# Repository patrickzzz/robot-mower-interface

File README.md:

# Robot Mower Interface

## Overview
This project provides an interface for controlling and managing a robot mower.

Initially this is done for a Ferrex R800Easy+ robot mower (meaning, it will be probably easily adaptable to other models from Ferrex, Yard Force (Yardforce), Garden Feelings and so on). 

## Original Goals
- The mower lacks the possibility to mow less than 4 hours a day. Also it has no app to control it (other models may have an app, but only closed source). These are the main reasons for this project.
- The main goal is a personal use case. There still might be errors in the project and/or in the documentation.

## Features
- **Control**: Execute Start, Home, Stop, and Lock on the mower.
- **Configuration**: Configure Wi-Fi settings (either connected to a Wifi, or as Access Point).
- **Scheduling**: Set mowing schedules.
- **Status**: View mower status
- **Logs**: See logs from the mower
- **API** Access all features via API
- **Web Interface** Access all features via a web interface
- **OTA Updates** Update the firmware and filesystem of the mower interface over the air (OTA) in Webinterface or API Endpoint.

## Demo of first running version

## License
This project is licensed under the Creative Commons Zero v1.0 Universal (CC0 1.0) - see the [LICENSE](LICENSE) file for details.

It's important to note that the original firmware of the mower is not open source, and this project is not affiliated with the manufacturer.
The original firmware of the mower is not changed in any way, but the warranty of the mower will be voided modifying the mower in this way.
I am not responsible for any damage to the mower or any other device.

## API Endpoint Documentation

### 1. `/start`
- **Method:** `POST`
- **Description:** Starts the mower.
- **Parameters:** None
- **Response:** `200 OK` if successful

### 2. `/home`
- **Method:** `POST`
- **Description:** Sends the mower back to the charging station.
- **Parameters:** None
- **Response:** `200 OK` if successful

### 3. `/stop`
- **Method:** `POST`
- **Description:** Stops the mower.
- **Parameters:** None
- **Response:** `200 OK` if successful

### 4. `/lock`
- **Method:** `POST`
- **Description:** Locks the mower.
- **Parameters:** None
- **Response:** `200 OK` if successful

### 5. `/unlock`
- **Method:** `POST`
- **Description:** Unlocks the mower.
- **Parameters:** None
- **Response:** `200 OK` if successful

### 6. `/status`
- **Method:** `GET`
- **Description:** Returns the current status of the mower.
- **Parameters:** None
- **Response:** JSON object with the following fields:
    - `date`: Current date on the mower
    - `time`: Current time on the mower
    - `isCharging`: Charging status
    - `isLocked`: Lock status
    - `isEmergency`: Emergency status
    - `isIdle`: Idle status
    - `isAccessPoint`: Access Point mode status
    - `hostname`: Hostname of the mower
    - `ssid`: Current WiFi SSID
    - `ip`: IP address of the mower
    - `mowingPlanActive`: Indicates if the mowing plan is active

### 7. `/mowing-plan`
- **Method:** `GET`
- **Description:** Retrieves the current mowing plan.
- **Parameters:** None
- **Response:** JSON file of the mowing plan if exists, or `204 No Content` if not found

### 8. `/mowing-plan`
- **Method:** `POST`
- **Description:** Sets a new mowing plan.
- **Payload:** JSON object with the following fields:
    - `customMowingPlanActive` (boolean): Activates or deactivates the custom mowing plan
    - `days` (array of booleans): Specifies active days (Mon-Sun)
    - `planTimeStart` (string): Mowing start time (e.g., `"09:00"`)
    - `planTimeEnd` (string): Mowing end time (e.g., `"17:00"`)
- **Response:** `200 OK` if successful, `400 Bad Request` if parameters are missing

### 9. `/wifis`
- **Method:** `GET`
- **Description:** Returns a list of available WiFi networks.
- **Parameters:** None
- **Response:** JSON array with SSIDs of the detected networks

### 10. `/wifi`
- **Method:** `POST`
- **Description:** Sets the WiFi credentials for the mower to connect to.
- **Payload:** JSON object with the following fields:
    - `ssid` (string): WiFi SSID
    - `password` (string): WiFi password
- **Response:** `200 OK` if successful, `400 Bad Request` if parameters are missing

### 11. `/date-time`
- **Method:** `POST`
- **Description:** Sets the date and time on the mower.
- **Payload:** JSON object with the following fields:
    - `date` (string): Date in the format `YYYY-MM-DD`
    - `time` (string): Time in the format `HH:MM`
- **Response:** `200 OK` if successful, `400 Bad Request` if parameters are missing

### 12. `/update`
- **Method:** `POST`
- **Description:** Allows for simultaneous upload and update of both firmware and filesystem files on the device. This endpoint manages both types of updates, determining the file type based on the filename.
- **Payload:** Multipart form-data with up to two files:
  - `firmware.bin`: Firmware binary file for updating the main program.
  - `filesystem.bin`: Filesystem binary file (e.g., SPIFFS) for updating the file system.
- **Response:**
  - **`200 OK`**: Returns `"Update Success!"` if the upload and update process are successful for both files.
  - **`500 Internal Server Error`**: Returns `"Update Failed!"` if an error occurs during either update.
- **Usage Notes:**
  - **File Recognition**: The update type is determined by the filename—`firmware.bin` for firmware updates and `filesystem.bin` for filesystem updates.
  - **Restart**: Upon successful updates, the device automatically restarts to apply changes.

## Needed parts
- Ferrex R800Easy+ robot mower (or similar)
- ESP32 (e.g., ESP32 DevKitC)
- USB cable
- DC-DC step-down converter (~32V -> 5V)

## Software Installation Instructions
Follow these steps to install the mower control software on your ESP32:

- **Connect** your ESP32 to your computer via USB.
- **Clone** this Repository
- **Install** PlatformIO (if not installed)
- **Upload the File System:** In the project/backend directory, upload the filesystem to the ESP32 by running:
  ```bash
  pio run --target uploadfs
  ```
- **Upload the Firmware:** In the project/backend directory, upload the firmware to the ESP32:
  ```bash
  pio run --target upload
  ```

- **Verify Installation:** Once complete, the ESP32 should be ready to run with the mower control software, creating a Wifi Access Point with SSID "Robot Mower" and password: "MowerInterface".
- **While still connected with USB to the ESP32, open a Serial Monitor** and you should see the IP address of the ESP32. Use this IP address to access the web interface.
  ```bash
  pio device monitor
  ```

## Hardware Installation Instructions
- For now the ESP32 has to be powered from the mainboard, and several pins of the ESP32 have to be connected to the Cover-User-Interface-Board (CoverUI).
- The power (24V) will come from red J18 connector. This is constant and is not powered down in idle mode. Connect it to the DC-DC step-down converter and set this to 5V.
- The ESP32 will be powered from the 5V output of the DC-DC step-down converter.
- The Stop1 (J8) cable on the main board for now has to be disconnected. The bottom Stop button of the mower will not work anymore. The top Stop button will still work.
- The connection of the pins of the ESP32 will for now not be described here, but hopefully can be seen in the following pictures, or derived from the code.

## Photos

## Thanks To
Special thanks to the following projects and contributors:
- **[apehaenger/CoverUI](https://github.com/apehaenger/CoverUI)** — for extensive help on the mower and detailed documentation.
- **[ClemensElflein/OpenMower](https://github.com/ClemensElflein/OpenMower)** — for the inspiration behind this project.
- **[cedbossneo/Mowgli](https://github.com/cedbossneo/Mowgli)** — for mainboard documentation and insights.

And a big thanks to all contributors from these projects, as well as the developers of the hardware and software used in this project.

Last but not least, to my girlfriend and family for their patience and support during my development time.

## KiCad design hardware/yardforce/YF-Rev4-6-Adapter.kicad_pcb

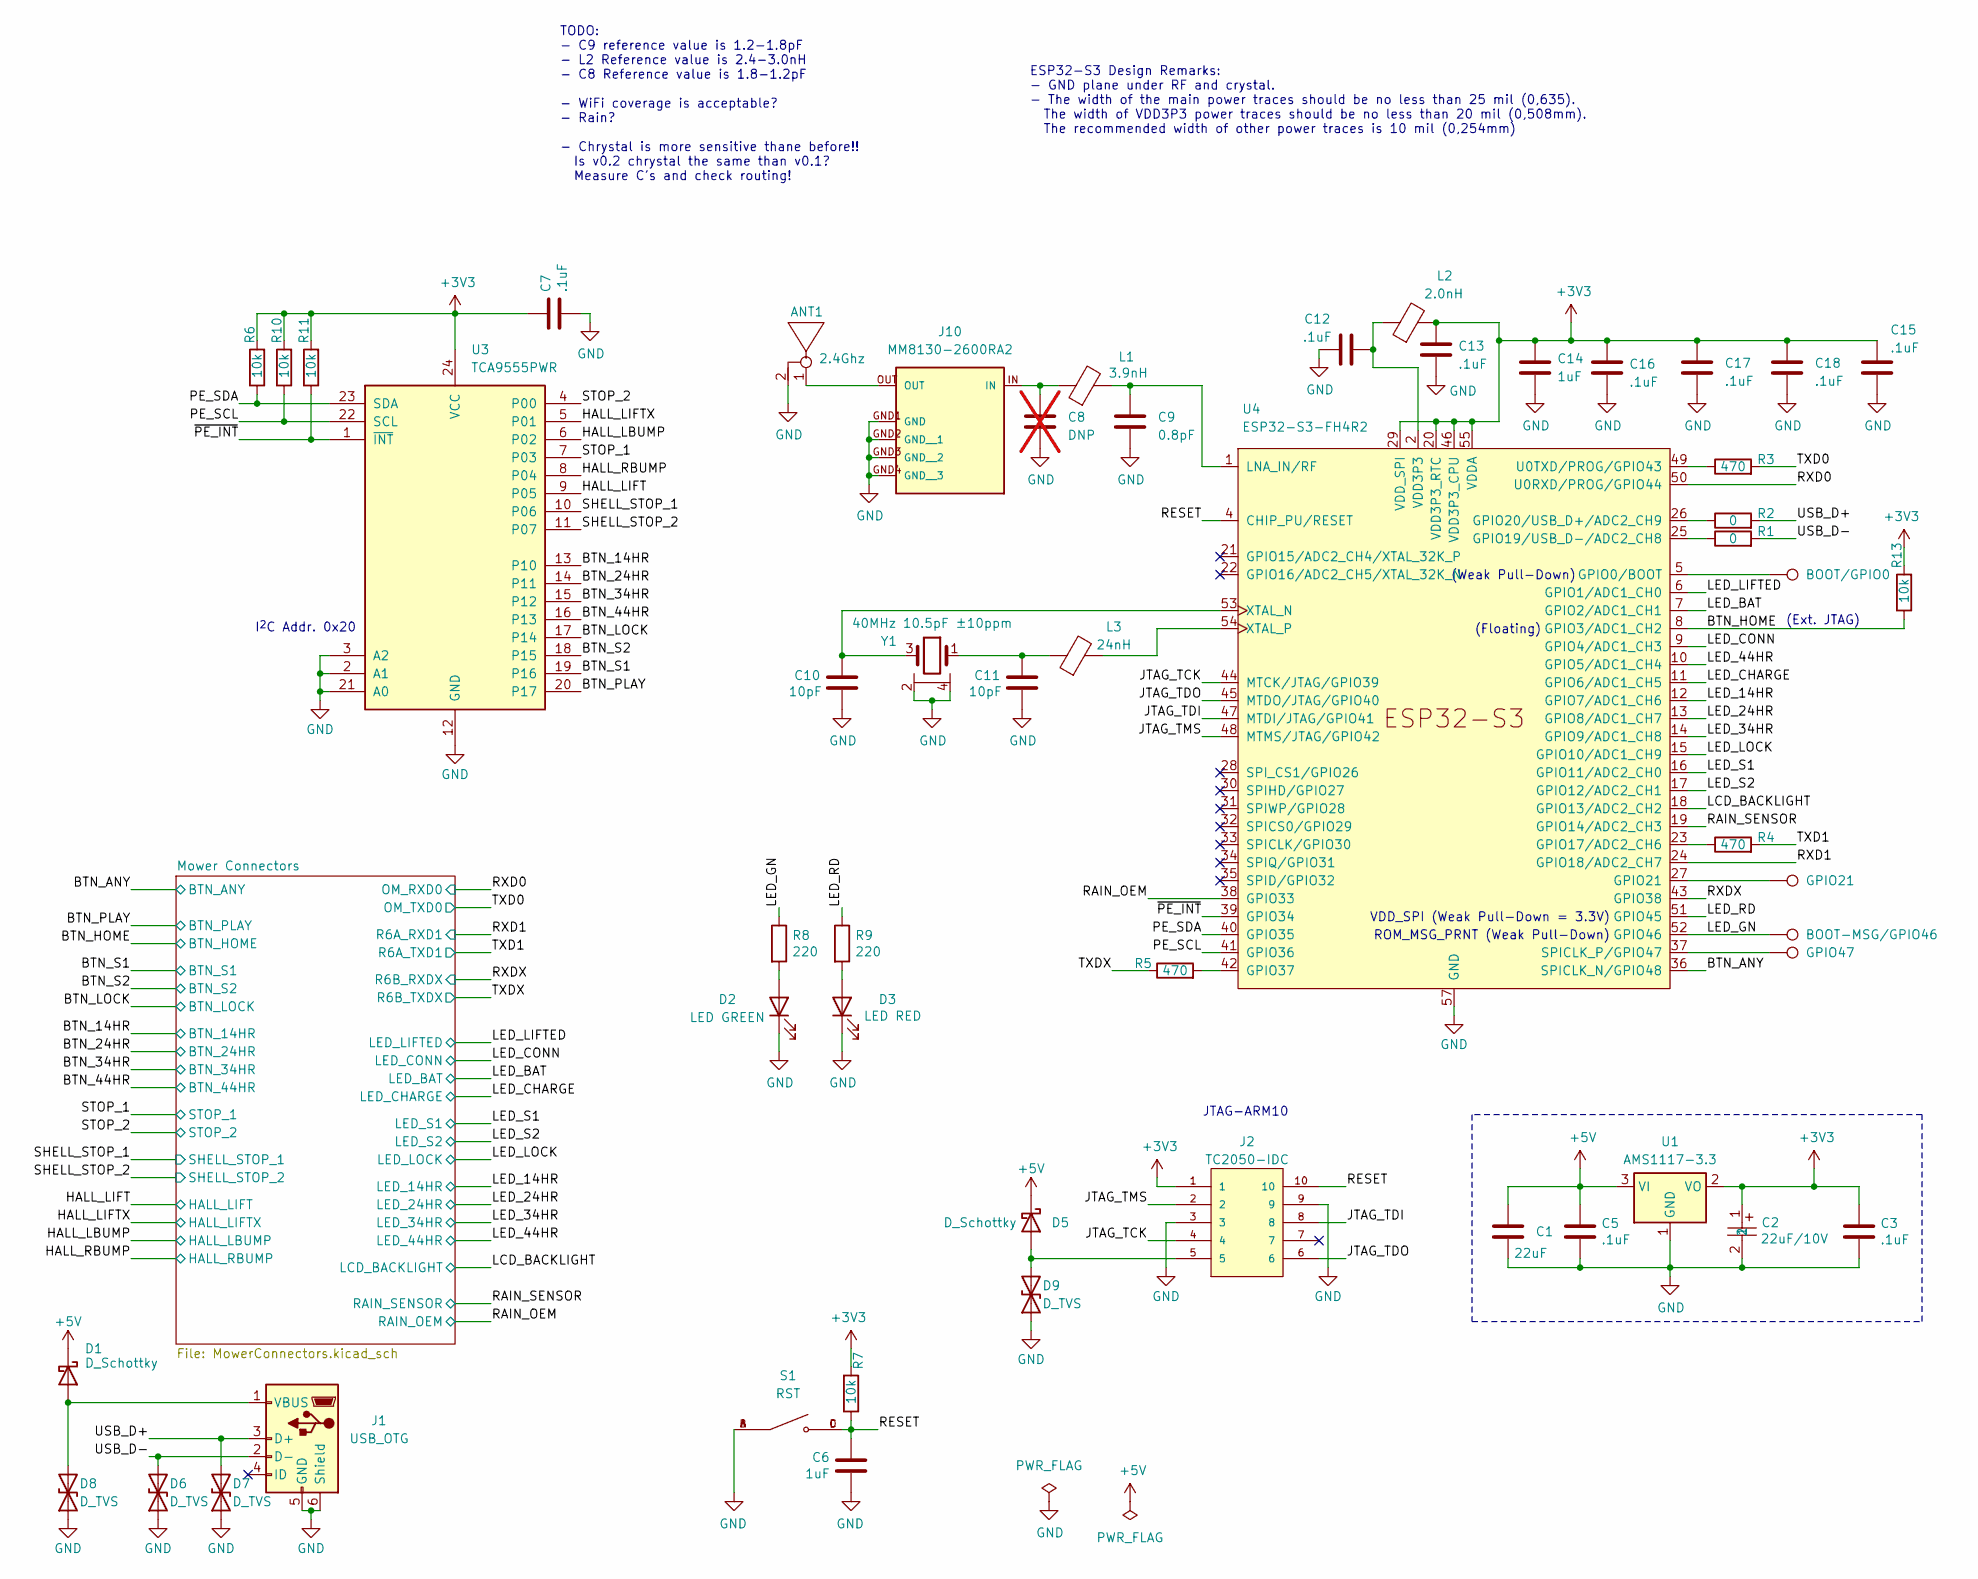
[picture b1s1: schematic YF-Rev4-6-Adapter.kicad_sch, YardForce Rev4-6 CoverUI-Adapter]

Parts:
ANT1: 2.4Ghz; PCB_Antenna_2.4GHz_Left
BOOT-MSG/GPIO46: TestPoint; TestPoint_Pad_1.0x1.0mm
BOOT/GPIO0: TestPoint; TestPoint_Pad_1.0x1.0mm
C1: 22uF; C_0805_2012Metric; LCSC C45783
C2: 22uF/10V; CASE-A_3216; LCSC C129272
C3, C5, C7, C12, C13, C15, C16, C17, C18: .1uF; C_0402_1005Metric; LCSC C1525
C6, C14: 1uF; C_0402_1005Metric; LCSC C52923
C8: DNP; C_0402_1005Metric; not fitted
C9: 0.8pF; C_0402_1005Metric; LCSC C5448872
C10, C11: 10pF; C_0402_1005Metric; MFR Part 0402CG140J500NT; LCSC C32949
D1, D5: D_Schottky; D_SOD-123; Part Number 1N5819HW-7-F; LCSC C82544
D2: LED GREEN; LED_0603_1608Metric; Part Number LTST-C191KGKT; Digikey 160-1446-1-ND
D3: LED RED; LED_0603_1608Metric; Part Number LTST-C191KRKT; Digikey 160-1447-1-ND
D6, D7, D8, D9: D_TVS; D_SOD-523; Part-Nr LESD5D5.0CT1G; LCSC C5449097
GPIO21, GPIO47: TestPoint; TestPoint_Pad_1.0x1.0mm
J1: USB_OTG; MINI-USB-SMD_U255-051N-4BH70-XS; LCSC C437033
J2: TC2050-IDC; TAG-CONNECT_TC2050-IDC; PARTREV A
J10: MM8130-2600RA2; MURATA_MM8130-2600RA2; LCSC C91633
L1: 3.9nH; L_0402_1005Metric; LCSC C370223
L2: 2.0nH; L_0402_1005Metric; LCSC C963978
L3: 24nH; L_0402_1005Metric; MFR Part SDCL1005C24NJTDF; LCSC C401493
R1, R2: 0; R_0402_1005Metric; LCSC C17168
R3, R4, R5: 470; R_0603_1608Metric; LCSC C23179
R6, R7, R10, R11, R13: 10k; R_0603_1608Metric; LCSC C25804
R8, R9: 220; R_0603_1608Metric; LCSC C22962
S1: RST; SW_TS-1187A-B-A-B; PARTREV A0; LCSC C318884
U1: AMS1117-3.3; SOT-223-3_TabPin2; LCSC C6186
U3: TCA9555PWR; TSSOP-24_4.4x7.8mm_P0.65mm; LCSC C465732
U4: ESP32-S3-FH4R2; QFN-56-1EP_7x7mm_P0.4mm_EP4x4mm_ThermalVias; LCSC C3013940
Y1: 40MHz 10.5pF ±10ppm; Crystal_SMD_2016-4Pin_2.0x1.6mm; MF Part K2B4000010510; LCSC C18209006

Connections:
+3V3: C2.1, C3.1, C7.1, C13.1, C14.1, C15.1, C16.1, C17.1, C18.1, J2.1, L2.2, R6.2, R7.2, R10.2, R11.2, R13.2, U1.2 (VO), U3.24 (VCC), U4.20 (VDD3P3_RTC), U4.29 (VDD_SPI), U4.46 (VDD3P3_CPU), U4.55 (VDDA), U4.56 (VDDA); also elsewhere on the board
+5V: C1.1, C5.1, D1.1 (K), D5.1 (K), U1.3 (VI); also elsewhere on the board
/BTN_14HR: U3.13 (P10); also elsewhere on the board
/BTN_24HR: U3.14 (P11); also elsewhere on the board
/BTN_34HR: U3.15 (P12); also elsewhere on the board
/BTN_44HR: U3.16 (P13); also elsewhere on the board
/BTN_ANY: U4.36 (SPICLK_N/GPIO48); also elsewhere on the board
/BTN_HOME: R13.1, U4.8 (GPIO3/ADC1_CH2); also elsewhere on the board
/BTN_LOCK: U3.17 (P14); also elsewhere on the board
/BTN_PLAY: U3.20 (P17); also elsewhere on the board
/BTN_S1: U3.19 (P16); also elsewhere on the board
/BTN_S2: U3.18 (P15); also elsewhere on the board
/HALL_LBUMP: U3.6 (P02); also elsewhere on the board
/HALL_LIFT: U3.9 (P05); also elsewhere on the board
/HALL_LIFTX: U3.5 (P01); also elsewhere on the board
/HALL_RBUMP: U3.8 (P04); also elsewhere on the board
/JTAG_TCK: J2.4, U4.44 (MTCK/JTAG/GPIO39)
/JTAG_TDI: J2.8, U4.47 (MTDI/JTAG/GPIO41)
/JTAG_TDO: J2.6, U4.45 (MTDO/JTAG/GPIO40)
/JTAG_TMS: J2.2, U4.48 (MTMS/JTAG/GPIO42)
/LCD_BACKLIGHT: U4.18 (GPIO13/ADC2_CH2); also elsewhere on the board
/LED_14HR: U4.12 (GPIO7/ADC1_CH6); also elsewhere on the board
/LED_24HR: U4.13 (GPIO8/ADC1_CH7); also elsewhere on the board
/LED_34HR: U4.14 (GPIO9/ADC1_CH8); also elsewhere on the board
/LED_44HR: U4.10 (GPIO5/ADC1_CH4); also elsewhere on the board
/LED_BAT: U4.7 (GPIO2/ADC1_CH1); also elsewhere on the board
/LED_CHARGE: U4.11 (GPIO6/ADC1_CH5); also elsewhere on the board
/LED_CONN: U4.9 (GPIO4/ADC1_CH3); also elsewhere on the board
/LED_GN: BOOT-MSG/GPIO46.1, R8.1, U4.52 (GPIO46)
/LED_LIFTED: U4.6 (GPIO1/ADC1_CH0); also elsewhere on the board
/LED_LOCK: U4.15 (GPIO10/ADC1_CH9); also elsewhere on the board
/LED_RD: R9.1, U4.51 (GPIO45)
/LED_S1: U4.16 (GPIO11/ADC2_CH0); also elsewhere on the board
/LED_S2: U4.17 (GPIO12/ADC2_CH1); also elsewhere on the board
/PE_SCL: R10.1, U3.22 (SCL), U4.41 (GPIO36)
/PE_SDA: R6.1, U3.23 (SDA), U4.40 (GPIO35)
/RAIN_OEM: U4.38 (GPIO33); also elsewhere on the board
/RAIN_SENSOR: U4.19 (GPIO14/ADC2_CH3); also elsewhere on the board
/RESET: C6.1, J2.10, R7.1, S1.C, S1.D, U4.4 (CHIP_PU/RESET)
/RXD0: U4.50 (U0RXD/PROG/GPIO44); also elsewhere on the board
/RXD1: U4.24 (GPIO18/ADC2_CH7); also elsewhere on the board
/RXDX: U4.43 (GPIO38); also elsewhere on the board
/SHELL_STOP_1: U3.10 (P06); also elsewhere on the board
/SHELL_STOP_2: U3.11 (P07); also elsewhere on the board
/STOP_1: U3.7 (P03); also elsewhere on the board
/STOP_2: U3.4 (P00); also elsewhere on the board
/TXD0: R3.2; also elsewhere on the board
/TXD1: R4.2; also elsewhere on the board
/TXDX: R5.1; also elsewhere on the board
/USB_D+: D7.2 (A2), J1.3 (D+), R2.2
/USB_D-: D6.2 (A2), J1.2 (D-), R1.2
/~PE_INT: R11.1, U3.1 (~INT), U4.39 (GPIO34)
GND: ANT1.2, C1.2, C2.2, C3.2, C5.2, C6.2, C7.2, C8.2, C9.2, C10.2, C11.2, C12.1, C13.2, C14.2, C15.2, C16.2, C17.2, C18.2, D2.1 (K), D3.1 (K), D6.1 (A1), D7.1 (A1), D8.1 (A1), D9.1 (A1), J1.5 (GND), J1.6 (Shield), J2.3, J2.9, J10.GND1 (GND), J10.GND2 (GND__1), J10.GND3 (GND__2), J10.GND4 (GND__3), S1.A, S1.B, U1.1 (GND), U3.2 (A1), U3.3 (A2), U3.12 (GND), U3.21 (A0), U4.57 (GND), Y1.2, Y1.4; also elsewhere on the board
unnamed: ANT1.1, J10.OUT
unnamed: C8.1, J10.IN, L1.1
unnamed: C11.1, L3.1, Y1.1
unnamed: D1.2 (A), D8.2 (A2), J1.1 (VBUS)
unnamed: D2.2 (A), R8.2
unnamed: D3.2 (A), R9.2
unnamed: D5.2 (A), D9.2 (A2), J2.5
unnamed: BOOT/GPIO0.1, U4.5 (GPIO0/BOOT)
unnamed: R4.1, U4.23 (GPIO17/ADC2_CH6)
unnamed: R1.1, U4.25 (GPIO19/USB_D-/ADC2_CH8)
unnamed: R2.1, U4.26 (GPIO20/USB_D+/ADC2_CH9)
unnamed: GPIO21.1, U4.27 (GPIO21)
unnamed: R5.2, U4.42 (GPIO37)
unnamed: C9.1, L1.2, U4.1 (LNA_IN/RF)
unnamed: GPIO47.1, U4.37 (SPICLK_P/GPIO47)
unnamed: R3.1, U4.49 (U0TXD/PROG/GPIO43)
unnamed: C10.1, U4.53 (XTAL_N), Y1.3
unnamed: L3.2, U4.54 (XTAL_P)
VDD3P3: C12.2, L2.1, U4.2 (VDD3P3), U4.3 (VDD3P3)

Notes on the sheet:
(Floating)
ESP32-S3 Design Remarks: - GND plane under RF and crystal. - The width of the main power traces should be no less than 25 mil (0,635). The width of VDD3P3 power traces should be no less than 20 mil (0,508mm). The recommended width of other power traces is 10 mil (0,254mm)
ROM_MSG_PRNT (Weak Pull-Down)
(Weak Pull-Down)
JTAG-ARM10
(Ext. JTAG)
VDD_SPI (Weak Pull-Down = 3.3V)
I^{2}C Addr. 0x20
TODO: - C9 reference value is 1.2-1.8pF - L2 Reference value is 2.4-3.0nH - C8 Reference value is 1.8-1.2pF - WiFi coverage is acceptable? - Rain? - Chrystal is more sensitive thane before!! Is v0.2 chrystal the same than v0.1? Measure C's and check routing!

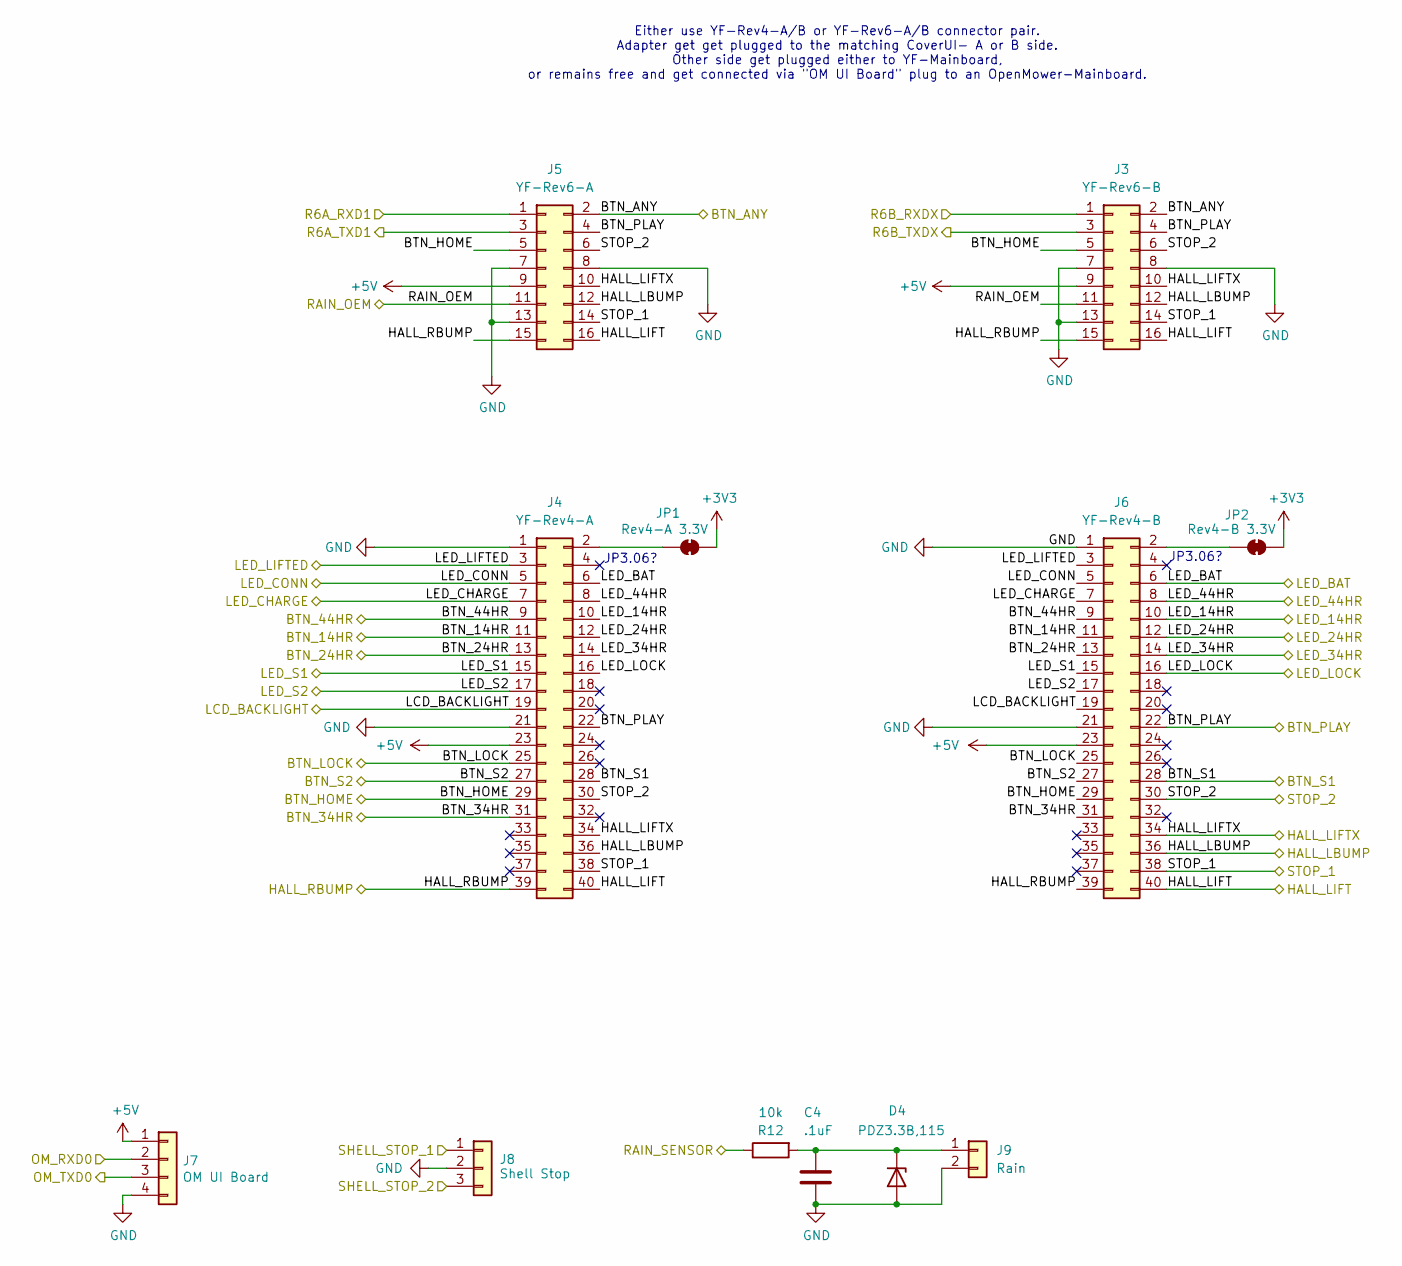
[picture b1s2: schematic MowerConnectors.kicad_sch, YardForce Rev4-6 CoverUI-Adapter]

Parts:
C4: .1uF; C_0402_1005Metric; JLC C307331
D4: PDZ3.3B,115; D_SOD-323; JLC C426855
J3: YF-Rev6-B; IDC-Hybrid_2x08_P2.54mm_Latch_Vertical; DigiKey S9196-ND
J4: YF-Rev4-A; IDC-Hybrid_2x20_P2.54mm_Latch_Vertical; DigiKey SFH11-PBPC-D20-ST-BK
J5: YF-Rev6-A; IDC-Hybrid_2x08_P2.54mm_Latch_Vertical; DigiKey S9196-ND
J6: YF-Rev4-B; IDC-Hybrid_2x20_P2.54mm_Latch_Vertical; DigiKey SFH11-PBPC-D20-ST-BK
J7: OM UI Board; JST_XH_B4B-XH-A_1x04_P2.50mm_Vertical; Part Number B4B-XH-A(LF)(SN); Digikey 455-2249-ND
J8: Shell Stop; JST_XH_B3B-XH-A_1x03_P2.50mm_Vertical; Part Number B3B-XH-A(LF)(SN); LCSC C144394
J9: Rain; JST_XH_B2B-XH-A_1x02_P2.50mm_Vertical; Part Number ZX-XH2.54-2PZZ; LCSC C7429632
JP1: Rev4-A 3.3V; SolderJumper-2_P1.3mm_Bridged_RoundedPad1.0x1.5mm
JP2: Rev4-B 3.3V; SolderJumper-2_P1.3mm_Bridged_RoundedPad1.0x1.5mm
R12: 10k; R_0603_1608Metric; JLC C25744

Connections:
+3V3: JP1.2 (B), JP2.2 (B); also elsewhere on the board
+5V: J3.9, J4.23, J5.9, J6.23, J7.1; also elsewhere on the board
/BTN_14HR: J4.11, J6.11; also elsewhere on the board
/BTN_24HR: J4.13, J6.13; also elsewhere on the board
/BTN_34HR: J4.31, J6.31; also elsewhere on the board
/BTN_44HR: J4.9, J6.9; also elsewhere on the board
/BTN_ANY: J3.2, J5.2; also elsewhere on the board
/BTN_HOME: J3.5, J4.29, J5.5, J6.29; also elsewhere on the board
/BTN_LOCK: J4.25, J6.25; also elsewhere on the board
/BTN_PLAY: J3.4, J4.22, J5.4, J6.22; also elsewhere on the board
/BTN_S1: J4.28, J6.28; also elsewhere on the board
/BTN_S2: J4.27, J6.27; also elsewhere on the board
/HALL_LBUMP: J3.12, J4.36, J5.12, J6.36; also elsewhere on the board
/HALL_LIFT: J3.16, J4.40, J5.16, J6.40; also elsewhere on the board
/HALL_LIFTX: J3.10, J4.34, J5.10, J6.34; also elsewhere on the board
/HALL_RBUMP: J3.15, J4.39, J5.15, J6.39; also elsewhere on the board
/LCD_BACKLIGHT: J4.19, J6.19; also elsewhere on the board
/LED_14HR: J4.10, J6.10; also elsewhere on the board
/LED_24HR: J4.12, J6.12; also elsewhere on the board
/LED_34HR: J4.14, J6.14; also elsewhere on the board
/LED_44HR: J4.8, J6.8; also elsewhere on the board
/LED_BAT: J4.6, J6.6; also elsewhere on the board
/LED_CHARGE: J4.7, J6.7; also elsewhere on the board
/LED_CONN: J4.5, J6.5; also elsewhere on the board
/LED_LIFTED: J4.3, J6.3; also elsewhere on the board
/LED_LOCK: J4.16, J6.16; also elsewhere on the board
/LED_S1: J4.15, J6.15; also elsewhere on the board
/LED_S2: J4.17, J6.17; also elsewhere on the board
/RAIN_OEM: J3.11, J5.11; also elsewhere on the board
/RAIN_SENSOR: R12.1; also elsewhere on the board
/RXD0: J7.2; also elsewhere on the board
/RXD1: J5.1; also elsewhere on the board
/RXDX: J3.1; also elsewhere on the board
/SHELL_STOP_1: J8.1; also elsewhere on the board
/SHELL_STOP_2: J8.3; also elsewhere on the board
/STOP_1: J3.14, J4.38, J5.14, J6.38; also elsewhere on the board
/STOP_2: J3.6, J4.30, J5.6, J6.30; also elsewhere on the board
/TXD0: J7.3; also elsewhere on the board
/TXD1: J5.3; also elsewhere on the board
/TXDX: J3.3; also elsewhere on the board
GND: C4.2, D4.2 (A), J3.7, J3.8, J3.13, J4.1, J4.21, J5.7, J5.8, J5.13, J6.1, J6.21, J7.4, J8.2, J9.2; also elsewhere on the board
unnamed: C4.1, D4.1 (K), J9.1, R12.2
unnamed: J4.2, JP1.1 (A)
unnamed: J6.2, JP2.1 (A)

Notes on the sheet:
JP3.06?
Either use YF-Rev4-A/B or YF-Rev6-A/B connector pair. Adapter get get plugged to the matching CoverUI- A or B side. Other side get plugged either to YF-Mainboard, or remains free and get connected via "OM UI Board" plug to an OpenMower-Mainboard.

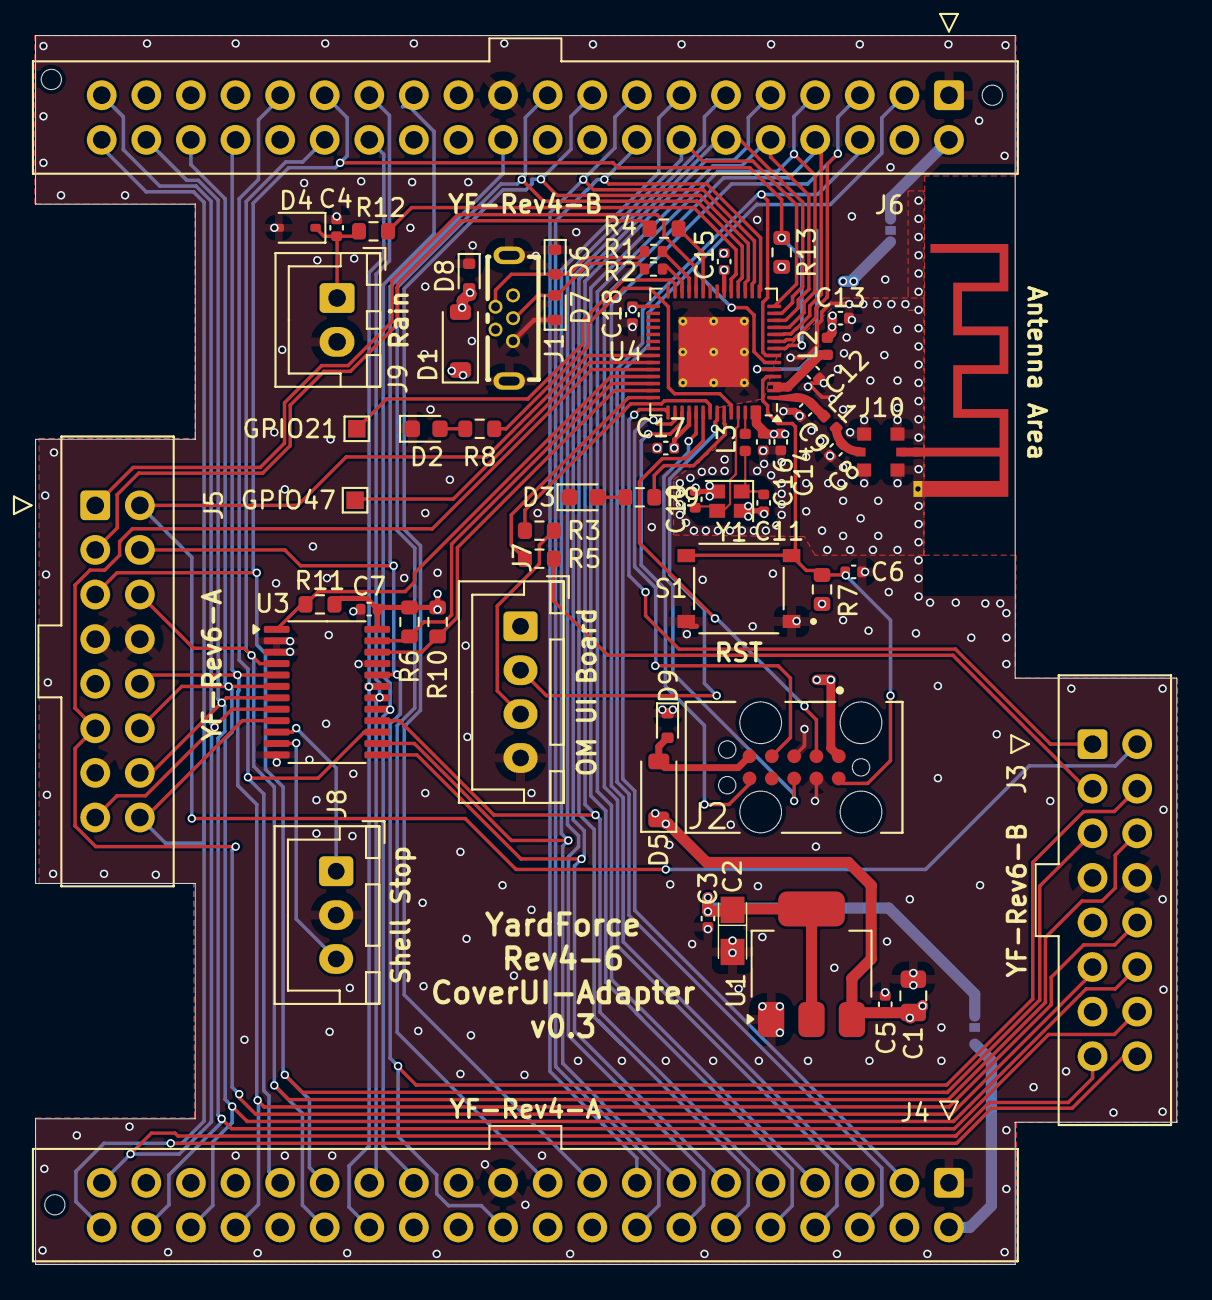
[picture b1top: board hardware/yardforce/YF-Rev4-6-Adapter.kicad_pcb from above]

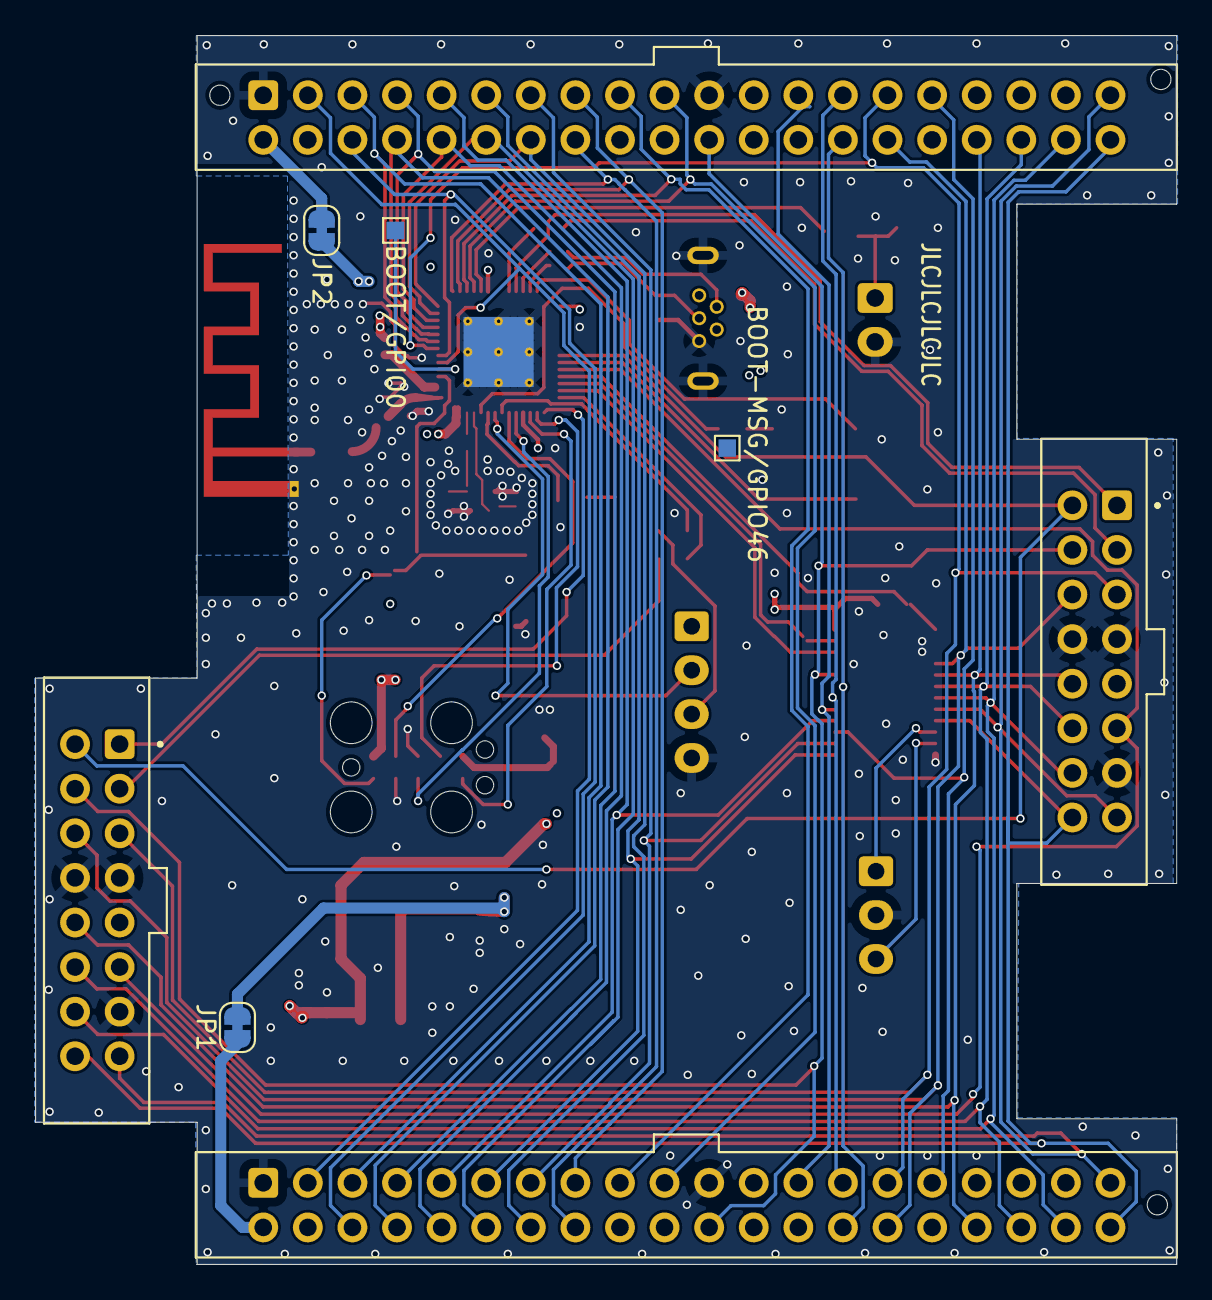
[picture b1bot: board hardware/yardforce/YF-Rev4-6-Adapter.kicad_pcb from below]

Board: 4 copper layers, 65.0 x 70.0 mm, 65 parts (4 on the bottom side), 75 nets.

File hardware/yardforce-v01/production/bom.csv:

Designator,Footprint,Quantity,Value,LCSC Part #
"C1, C2",0603,2,10uF,C19702
"C10, C11",0402,2,10pF,C32949
"C12, C15, C16, C17, C18, C3, C4, C7",0402,8,.1uF,C1525
"C14, C6",0402,2,1uF,C52923
C9,0402,1,0.8pF,C5448872
D1,D_SOD-123,1,D_Schottky,C82288
D2,0603,1,LED GREEN,C12624
D3,0603,1,LED RED,C2286
D4,D_SOD-323,1,"PDZ3.3B,115",C426855
J1,USB_Micro-B_Wuerth_614105150721_Vertical,1,USB_OTG,C668588
J7,JST_XH_B4B-XH-A_1x04_P2.50mm_Vertical,1,OM UI Board,C144395
J8,JST_XH_B3B-XH-A_1x03_P2.50mm_Vertical,1,Shell Stop,C144394
J9,JST_XH_B2B-XH-A_1x02_P2.50mm_Vertical,1,Rain,C2910525
L1,0402,1,3.9nH,C370223
L2,0402,1,2.0nH,C963978
L3,0402,1,24nH,C401493
"R1, R2",0402,2,0,C17168
"R10, R11, R12, R6, R7",0603,5,10k,C25804
"R3, R4, R5",0603,3,22	,C23345
R8,0603,1,200	,C8218
R9,0603,1,220,C22962
S1,SW_TS-1187A-B-A-B,1,RST,C318884
U1,SOT-223-3_TabPin2,1,AMS1117-3.3,C6186
U3,TSSOP-24_4.4x7.8mm_P0.65mm,1,TCA9555PWR,C465732
U4,QFN-56-1EP_7x7mm_P0.4mm_EP4x4mm_ThermalVias,1,ESP32-S3-FH4R2,C3013940
Y1,Crystal_SMD_2016-4Pin_2.0x1.6mm,1,40MHz 10.5pF ±10ppm,C18209006
